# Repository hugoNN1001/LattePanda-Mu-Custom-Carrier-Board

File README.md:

## What is it?
In an attempt to pick up some high-speed PCB skills before jumping onto my own personal high-speed project, I decided to buy a course from Tech Explorations and start from there. The project was a custom carrier board for the LattePanda Mu compute module.

The most important I learned from this project was about differential pairs routing, from sizing traces to the correct impedance depending on the stack-up, to preventing crosstalk, to matching trace length and preventing timing skew, to maintaining continuous reference plan and return path, as well as getting somewhat familiar to high-speed protocols like PCIe, Gbe Ethernet, USB3.9, HDMI, etc.

I have also decided to buy [another course](https://fedevel.com/courses/advanced-digital-hardware-design) on the same topic from Phil's Lab (there goes my wallet). This time, however, I won't be following the course and build a whole FPGA/SOC PCB. Instead, I will be using it as a guide to work on my upcoming project, which is going to be something about eDP or some other protocols to connect my laptop to a bare monitor. Can't wait!

## Status
18/09/2026

I have been grinding on the layout for the past few days. Last night, I let my laptop die without properly saving and closing the PCB editor. When I found out this morning that the layout work I had been working on was completely lost, I quickly checked the backup files.

To my surprise, there was none. I then found out that the automatic backup feature was not enabled. So now I am left with nothing to show for my work. At least now, my only comfort is the stuff I was able to learn about high-speed PCB design throughout this project.

In my original layout, USB3.0/2.0, Ethernet, HDMI, M.2 E&M Key, GPIO, I2C, UART, as well as the PSU had been laid out.

Below are the links to the photos of the schematics and the (old) layout. Somehow the schematic window was able to close down properly before my laptop died so they are up to date.

## Photos
<table>
  <tr>
    <td></td>
    <td></td>
  </tr>
  <tr>
    <td></td>
    <td></td>
  </tr>
  <tr>
    <td></td>
    <td></td>
  </tr>
  <tr>
    <td></td>
    <td></td>
  </tr>
  <tr>
    <td></td>
    <td></td>
  </tr>
  <td></td>
  <td><em>Layout progress at time of loss (unsaved crash - see write-up)</em></td>
</table>

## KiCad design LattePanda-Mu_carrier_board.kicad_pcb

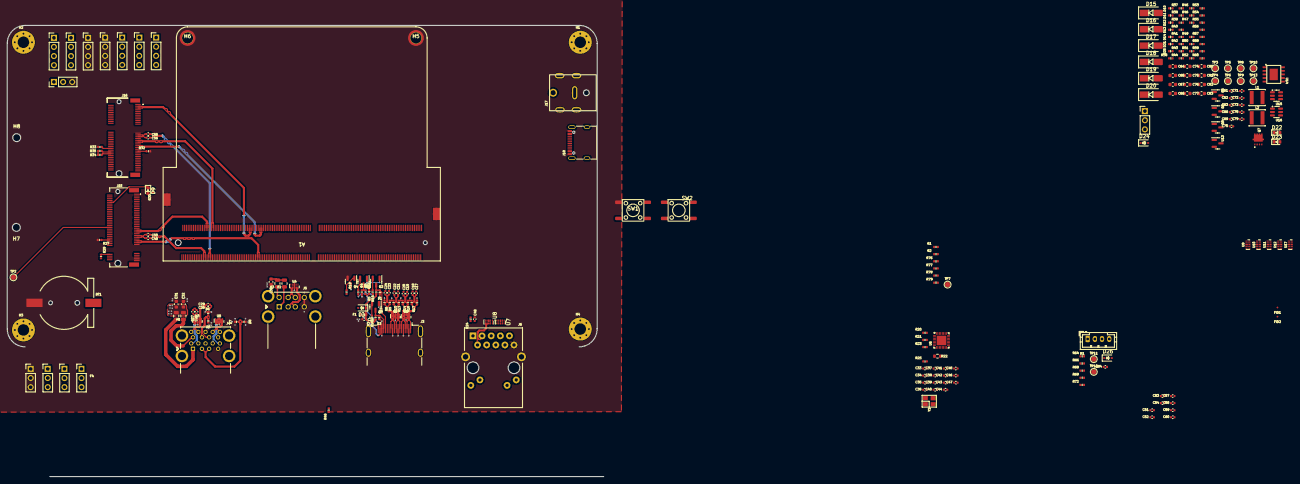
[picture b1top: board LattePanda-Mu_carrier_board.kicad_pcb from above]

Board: 4 copper layers, 240 parts (0 on the bottom side), 179 nets.

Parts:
A1: LattePanda_Mu; LattePanda_Module_H8.0mm_Horizontal
BT1: Battery_Cell; Battery_Holder_CR1220_S8411-45R
C17, C18, C19, C20, C21, C22, C23, C24, C25, C26, C27, C28, C29, C33, C34, C35, C36, C37, C38, C39, C40, C41, C42, C43, C45, C48, C52, C54, C58, C60, C70, C71, C84: 100nF/50V; C_0402_1005Metric
C30, C31, C32, C64, C65, C67, C68, C74, C75, C76, C77, C80, C81, C82, C83: 22uF/10V; C_0603_1608Metric
C44, C51, C53, C57, C59: 10uF/50V; C_0402_1005Metric
C46, C47, C72, C73: 12pF/50V; C_0402_1005Metric
C49, C50, C55, C56: 220nF/50V; C_0402_1005Metric
C61, C62, C63, C66: 1uF/16V; C_0402_1005Metric
C69: 1uF/10V; C_0402_1005Metric
C78, C79: 100nF/10V; C_0402_1005Metric
D1, D2, D3, D5, D6, D7, D8, D10, D11, D21: ESD5V0B03; D_0402_1005Metric
D4, D26: 1N5819WS; D_SOD-323
D9, D22, D23: LED_G; LED_0603_1608Metric
D12, D13, D14: PESD24VS1UL-N; D_0402_1005Metric
D15, D16, D17, D18, D19, D20: SS54; D_SMA
D24: 3V3 Izt=5mA; D_SOD-323
D25: ESD9B5.0ST5G; D_0402_1005Metric
F1: 6V/50mA; C_0603_1608Metric
F2, F3, F4, F5: 6V/1A; Fuse_0805_2012Metric
FID1, FID2: Fiducial; Fiducial_0.5mm_Mask1mm
H1, H2, H3, H4: MountingHole_Pad; MountingHole_3.2mm_M3_Pad_Via
H5, H6: MountingHole_Pad; MountingHole_3mm_M2_Pad_TopOnly
H7, H8: MountingHole_M2.0; MountingHole_2.2mm_M2
J1, J8, J10, J11, J14: Conn_01x03_Pin; PinHeader_1x03_P2.54mm_Vertical
J3: HDMI_A; HDMI_A_Molex_208658-1001_Horizontal
J4: USB3_A_Stacked; USB3_A_Molex_48406-0001_Horizontal_Stacked
J5: USB_A_Stacked; USB_A_CUI_UJ2-ADH-TH_Horizontal_Stacked
J6: RJ45_RB1-125B8G1A; RJ45_UDE_RB1-125B8G1A
J7, J9, J12, J13, J19, J20, J21: Conn_01x04_Pin; PinHeader_1x04_P2.54mm_Vertical
J15: Bus_M.2_Socket_M; PCIe_M.2_Connectors_P=0.5mm_H=4.2mm_KeyM
J16: Bus_M.2_Socket_E; PCIe_M.2_Connectors_P=0.5mm_H=4.2mm_KeyE
J17: Barrel_Jack_Switch; DC_Jack_DC007B_30V_10A
J18: USB_C_Receptacle_USB2.0_16P; USB_C_Receptacle_G-Switch_GT-USB-7010ASV
JP1: SolderJumper_3_Bridged12; PinHeader_1x03_P2.54mm_Vertical
L1, L2: 2.2uH/4.3A; L_Sunlord_SWPA4020S
M1: Fan_4pin; JST_PH_B4B-PH-K_1x04_P2.00mm_Vertical
Q1, Q5, Q6, Q8: 2N7002; SOT-23
Q2, Q3, Q4: 2SK3018; SOT-23
Q7: AON7262E; MOSFET_PDFN8_3.3x3.3
R1, R11, R37, R47: 1k/1%; R_0402_1005Metric
R2, R20, R21, R34, R35, R36, R38, R40, R49, R50, R56, R58, R78, R79: 10k/1%; R_0402_1005Metric
R3, R5, R15, R18, R19, R39, R52, R53: 2.2k/1%; R_0402_1005Metric
R4, R23: 1M/1%; R_0402_1005Metric
R6, R41, R42, R54, R59, R66, R68: 21.5k/1%; R_0402_1005Metric
R7, R8, R9, R10, R13, R14, R16, R17, R24, R25: 470R/1%; R_0402_1005Metric
R22: 2.49k/1%; R_0603_1608Metric
R27, R29, R32, R33: 0R/1%; R_0402_1005Metric
R30: 2.2K/1%; R_0402_1005Metric
R43: 56k/1%; R_0402_1005Metric
R44, R45, R51, R76, R77: 100k/1%; R_0402_1005Metric
R46, R48, R55, R69: 100R/1%; R_0402_1005Metric
R57: 75k/1%; R_0402_1005Metric
R60, R64, R72: 4.7k/1%; R_0402_1005Metric
SW1: PWR_SW; SW_Push_6x6x6
SW2: RST_SW; SW_Push_6x6x6
TP2, TP3, TP4, TP5, TP6, TP7, TP8, TP9, TP10, TP11, TP12, TP13: TestPoint; TestPoint_Pad_D1.5mm
U1, U2: TPAZ1023-04F; Diodes_UDFN-10_1.0x2.5mm_P0.5mm
U3, U9, U10, U11, U12, U17: ULC0524P; Diodes_UDFN-10_1.0x2.5mm_P0.5mm
U4, U5: Diodes_UDFN-10_1.0x2.5mm_P0.5mm
U6: RTL8111H-CG-RH; QFN-32-1EP_4x4mm_P0.4mm_EP2.65x2.65mm
U7, U8: ULC0524P; Diodes_UDFN-10_1x2.5mm_P0.5mm
U13: TL431DBZ; SOT-23
U14: USB PD等快充协议受电芯片-CH224K-ESSOP10; ESSOP-10-1EP_3.9x5mm_P1.0mm_EP3.2x2.3
U15, U16: SY8253ADC; TSOT-23-6
Y1: 25Mhz; Crystal_SMD_3225-4Pin_3.2x2.5mm

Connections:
5V_HDMI_VCC: C25.1, D4.1 (K), F1.1, R15.1, R18.1
+1V0: C33.1, C34.1, C35.1, C36.1, C40.1, C44.1, U6.3 (AVDD10), U6.8 (AVDD10), U6.22 (DVDD10), U6.24 (REGOUT), U6.30 (AVDD10)
+3.3V: C37.1, C41.1, C45.1, C51.1, C52.1, C53.1, C54.1, C57.1, C58.1, C59.1, C60.1, C73.2, C75.2, C77.2, C79.2, C81.2, C83.2, J13.1, J13.2, J13.3, J13.4, J14.1, J14.2, J14.3, J15.2 (3.3V), J15.4 (3.3V), J15.12 (3.3V), J15.14 (3.3V), J15.16 (3.3V), J15.18 (3.3V), J15.70 (3.3V), J15.72 (3.3V), J15.74 (3.3V), J16.2 (3.3V), J16.4 (3.3V), J16.72 (3.3V), J16.74 (3.3V), J21.1, J21.2, J21.3, J21.4, L2.2, Q1.1 (G), Q2.1 (G), Q3.1 (G), R3.1, R4.2, R5.1, R20.2, R21.2, R24.2, R25.2, R30.2, R34.1, R35.1, R50.2, R52.2, R56.2, R59.2, R64.2, TP6.1 (1_1), U6.11 (AVDD33), U6.23 (VDDREG), U6.32 (AVDD33)
+5V: C30.1, C31.1, C32.1, C72.2, C74.2, C76.2, C78.2, C80.2, C82.2, C84.1, D4.2 (A), D26.1 (K), F2.2, F3.2, F4.2, F5.2, L1.2, M1.2 (+), R57.2, R72.1, TP5.1 (1_1)
+12V: C63.1, D15.2 (A), D16.2 (A), D17.2 (A), J17.1, Q7.1 (S_1), Q7.2 (S_2), Q7.3 (S_3), R38.2, R40.1, R44.1, TP4.1 (1_1)
+12VA: Q7.5 (D_1), Q7.6 (D_2), Q7.7 (D_3), Q7.8 (D_4), Q7.9 (D_5), Q7.10 (D_6), Q7.11 (D_7), R54.2, TP8.1 (1_1)
+15V: D14.1 (K), D18.2 (A), D19.2 (A), D20.2 (A), J18.A4 (VBUS), J18.A9 (VBUS), J18.B4 (VBUS), J18.B9 (VBUS), R36.1, R37.1, TP3.1 (1_1)
+BATT: A1.115 (VBAT), R1.1
/Fan/FAN1_PWM: A1.2 (FAN1_PWM), R64.1, R69.1, TP12.1 (1_1)
/Fan/FAN1_TAC: A1.4 (FAN1_TAC), R66.1, R68.1, TP11.1 (1_1)
/GPIO/GPP_D0: A1.128 (GPP_D0), J19.1, U17.1
/GPIO/GPP_D1: A1.130 (GPP_D1), J19.2, U17.2
/GPIO/GPP_D2: A1.132 (GPP_D2), J19.3, U17.4
/GPIO/GPP_D3: A1.134 (GPP_D3), J19.4, U17.5
/GPIO/I2C2_SCL: A1.154 (I2C2_SCL), J9.1, U11.1
/GPIO/I2C2_SDA: A1.156 (I2C2_SDA), J7.1, U9.1
/GPIO/I2C3_SCL: A1.150 (I2C3_SCL), J9.2, U11.2
/GPIO/I2C3_SDA: A1.152 (I2C3_SDA), J7.2, U9.2
/GPIO/I2C4_SCL: A1.146 (I2C4_SCL), J9.3, U11.4
/GPIO/I2C4_SDA: A1.148 (I2C4_SDA), J7.3, U9.4
/GPIO/I2C5_SCL: A1.142 (I2C5_SCL), J9.4, U11.5
/GPIO/I2C5_SDA: A1.144 (I2C5_SDA), J7.4, U9.5
/GPIO/SOC_UART0_RX: A1.137 (UART0_RXD), J8.1, U10.1, U12.1
/GPIO/SOC_UART0_TX: A1.139 (UART0_TXD), J10.1
/GPIO/SOC_UART1_RX: A1.141 (UART1_RXD), J8.2, U10.2, U12.2
/GPIO/SOC_UART1_TX: A1.143 (UART1_TXD), J10.2
/GPIO/SOC_UART2_RX: A1.140 (UART2_RXD), J8.3, U10.4, U12.4
/GPIO/SOC_UART2_TX: A1.138 (UART2_TXD), J10.3
/Gigabit Ethernet/GbE_PCIe_CLK+: A1.94 (REFCLK4+), U6.15 (REFCLK_P)
/Gigabit Ethernet/GbE_PCIe_CLK-: A1.96 (REFCLK4-), U6.16 (REFCLK_N)
/Gigabit Ethernet/GbE_PCIe_RX+: A1.64 (HSIO6_RX+), C43.1
/Gigabit Ethernet/GbE_PCIe_RX-: A1.66 (HSIO6_RX-), C39.1
/Gigabit Ethernet/GbE_PCIe_TX+: A1.61 (HSIO6_TX+), C42.1
/Gigabit Ethernet/GbE_PCIe_TX-: A1.63 (HSIO6_TX-), C38.1
/Gigabit Ethernet/HSI+: C42.2, U6.13 (HSIP)
/Gigabit Ethernet/HSI-: C38.2, U6.14 (HSIN)
/Gigabit Ethernet/HSO+: C43.2, U6.17 (HSOP)
/Gigabit Ethernet/HSO-: C39.2, U6.18 (HSON)
/Gigabit Ethernet/MDI0+: J6.R2 (TD1+), U6.1 (MDIP0), U8.5, U8.6 (NC)
/Gigabit Ethernet/MDI0-: J6.R3 (TD1-), U6.2 (MDIN0), U8.4, U8.7 (NC)
/Gigabit Ethernet/MDI1+: J6.R4 (TD2+), U6.4 (MDIP1), U8.2, U8.9 (NC)
/Gigabit Ethernet/MDI1-: J6.R5 (TD2-), U6.5 (MDIN1), U8.1, U8.10 (NC)
/Gigabit Ethernet/MDI2+: J6.R6 (TD3+), U6.6 (MDIP2), U7.5, U7.6 (NC)
/Gigabit Ethernet/MDI2-: J6.R7 (TD3-), U6.7 (MDIN2), U7.4, U7.7 (NC)
/Gigabit Ethernet/MDI3+: J6.R8 (TD4+), U6.9 (MDIP3), U7.2, U7.9 (NC)
/Gigabit Ethernet/MDI3-: J6.R9 (TD4-), U6.10 (MDIN3), U7.1, U7.10 (NC)
/HDMI/DDC_SCL: D1.2 (A2), J3.15 (SCL), Q2.3 (D), R15.2
/HDMI/DDC_SDA: D3.2 (A2), J3.16 (SDA), Q3.3 (D), R18.2
/HDMI/DDIB_HPD: A1.183 (DDIB_HPD), Q1.2 (S), R4.1
/HDMI/DDIB_TX0+: A1.217 (DDIB_TX0+), C17.1
/HDMI/DDIB_TX0-: A1.215 (DDIB_TX0-), C18.1
/HDMI/DDIB_TX1+: A1.211 (DDIB_TX1+), C19.1
/HDMI/DDIB_TX1-: A1.209 (DDIB_TX1-), C20.1
/HDMI/DDIB_TX2+: A1.205 (DDIB_TX2+), C21.1
/HDMI/DDIB_TX2-: A1.203 (DDIB_TX2-), C22.1
/HDMI/DDIB_TX3+: A1.199 (DDIB_TX3+), C23.1
/HDMI/DDIB_TX3-: A1.197 (DDIB_TX3-), C24.1
/HDMI/DDI_B_DDC_SCL: A1.171 (DDIB_DDC_SCL), Q2.2 (S), R5.2
/HDMI/DDI_B_DDC_SDA: A1.169 (DDIB_DDC_SDA), Q3.2 (S), R3.2
/HDMI/HPD: D2.2 (A2), J3.19 (HPD), R11.2
/HDMI/TMDS_CK+: C23.2, J3.10 (CK+), R8.1, U2.4, U2.7 (NC)
/HDMI/TMDS_CK-: C24.2, J3.12 (CK-), R7.1, U2.5, U2.6 (NC)
/HDMI/TMDS_D0+: C21.2, J3.7 (D0+), R10.1, U2.1, U2.10 (NC)
/HDMI/TMDS_D0-: C22.2, J3.9 (D0-), R9.1, U2.2, U2.9 (NC)
/HDMI/TMDS_D1+: C19.2, J3.4 (D1+), R14.1, U1.4, U1.7 (NC)
/HDMI/TMDS_D1-: C20.2, J3.6 (D1-), R13.1, U1.5, U1.6 (NC)
/HDMI/TMDS_D2+: C17.2, J3.1 (D2+), R17.1, U1.1, U1.10 (NC)
/HDMI/TMDS_D2-: C18.2, J3.3 (D2-), R16.1, U1.2, U1.9 (NC)
/LattePanda Mu Module/HSIO_0_TX+: A1.13 (HSIO0_TX+), C27.2
/LattePanda Mu Module/HSIO_0_TX-: A1.15 (HSIO0_TX-), C26.2
/LattePanda Mu Module/HSIO_1_TX+: A1.19 (HSIO1_TX+), C29.2
/LattePanda Mu Module/HSIO_1_TX-: A1.21 (HSIO1_TX-), C28.2
/LattePanda Mu Module/HSIO_2_RX+: A1.28 (HSIO2_RX+), J15.43 (PERp0/SATA-B-)
/LattePanda Mu Module/HSIO_2_RX-: A1.30 (HSIO2_RX-), J15.41 (PERn0/SATA-B+)
/LattePanda Mu Module/HSIO_2_TX+: A1.25 (HSIO2_TX+), C49.1
/LattePanda Mu Module/HSIO_2_TX-: A1.27 (HSIO2_TX-), C50.1
/LattePanda Mu Module/HSIO_3_RX+: A1.34 (HSIO3_RX+), J16.43 (PERn0)
/LattePanda Mu Module/HSIO_3_RX-: A1.36 (HSIO3_RX-), J16.41 (PERp0)
/LattePanda Mu Module/HSIO_3_TX+: A1.31 (HSIO3_TX+), C56.1
/LattePanda Mu Module/HSIO_3_TX-: A1.33 (HSIO3_TX-), C55.1
/LattePanda Mu Module/REFCLK0+: A1.85 (REFCLK0+), J15.55 (REFCLKp)
/LattePanda Mu Module/REFCLK0-: A1.87 (REFCLK0-), J15.53 (REFCLKn)
/LattePanda Mu Module/REFCLK3+: A1.88 (REFCLK3+), J16.47 (REFCLKp0)
/LattePanda Mu Module/REFCLK3-: A1.90 (REFCLK3-), J16.49 (REFCLKn0)
/LattePanda Mu Module/SLS_S3: A1.7 (SLS_S3), JP1.3 (B)
/LattePanda Mu Module/SUSCLK_WIFI: A1.131 (SUSCLK), R29.2
/LattePanda Mu Module/USB2_P7+: A1.76 (USB2_P7+), J16.3 (USB_D+)
/LattePanda Mu Module/USB2_P7-: A1.78 (USB2_P7-), J16.5 (USB_D-)
/LattePanda Mu Module/~PWR_SW: A1.1 (~PWRBTN), R48.2
/LattePanda Mu Module/~RST_SW: A1.3 (~RSTBTN), R55.2
/M.2 M Key/CON_PCIE_TX0+: C55.2, J16.35 (PETp0)
/M.2 M Key/CON_PCIE_TX0-: C56.2, J16.37 (PETn0)
/M.2 M Key/CON_PCIE_TX1+: C49.2, J15.49 (PETp0/SATA-A+)
/M.2 M Key/CON_PCIE_TX1-: C50.2, J15.47 (PETn0/SATA-A-)
/M.2 M Key/~CLKREQ_E: J16.53 (~CLKREQ0), R32.1
/M.2 M Key/~CLKREQ_M: J15.52 (~CLKREQ), R27.1
/Power Supply/CC1: D13.1 (K), J18.A5 (CC1), U14.7 (CC1)
/Power Supply/CC2: D12.1 (K), J18.B5 (CC2), U14.6 (CC2)
/Power Supply/PWR_C_D+: D11.2 (A2), J18.A7 (D-), J18.B7 (D-), U14.5 (DM)
/Power Supply/PWR_C_D-: D10.2 (A2), J18.A6 (D+), J18.B6 (D+), U14.4 (DP)
/Power Supply/PWR_EN: Q6.1 (G), R46.1, R51.2, TP9.1 (1_1), U15.4 (EN), U16.4 (EN)
/USB 2.0 &3.0/CON_USB1_D_N: A1.109 (USB2_P5-), J5.2 (D1-), U4.2, U4.9 (NC)
/USB 2.0 &3.0/CON_USB1_D_P: A1.111 (USB2_P5+), J5.3 (D1+), U4.1, U4.10 (NC)
/USB 2.0 &3.0/CON_USB2_D_N: A1.79 (USB2_P3-), J5.6 (D2-), U4.5, U4.6 (NC)
/USB 2.0 &3.0/CON_USB2_D_P: A1.81 (USB2_P3+), J5.7 (D2+), U4.4, U4.7 (NC)
/USB 2.0 &3.0/CON_USB3_D_N: A1.75 (USB2_P2+), D8.2 (A2), J4.2 (D1-)
/USB 2.0 &3.0/CON_USB3_D_P: A1.73 (USB2_P2-), D7.2 (A2), J4.3 (D1+)
/USB 2.0 &3.0/CON_USB3_SSRX_N: A1.18 (HSIO0_RX-), J4.5 (SSRX1-), U5.4, U5.7 (NC)
/USB 2.0 &3.0/CON_USB3_SSRX_P: A1.16 (HSIO0_RX+), J4.6 (SSRX1+), U5.5, U5.6 (NC)
/USB 2.0 &3.0/CON_USB3_SSTX_N: C26.1, J4.8 (SSTX1-), U3.4, U3.7 (NC)
/USB 2.0 &3.0/CON_USB3_SSTX_P: C27.1, J4.9 (SSTX1+), U3.5, U3.6 (NC)
/USB 2.0 &3.0/CON_USB4_D_N: A1.67 (USB2_P1-), D6.2 (A2), J4.11 (D2-)
/USB 2.0 &3.0/CON_USB4_D_P: A1.69 (USB2_P1+), D5.2 (A2), J4.12 (D2+)
/USB 2.0 &3.0/CON_USB4_SSRX_N: A1.24 (HSIO1_RX-), J4.14 (SSRX2-), U5.1, U5.10 (NC)
/USB 2.0 &3.0/CON_USB4_SSRX_P: A1.22 (HSIO1_RX+), J4.15 (SSRX2+), U5.2, U5.9 (NC)
/USB 2.0 &3.0/CON_USB4_SSTX_N: C28.1, J4.17 (SSTX2-), U3.1, U3.10 (NC)
/USB 2.0 &3.0/CON_USB4_SSTX_P: C29.1, J4.18 (SSTX2+), U3.2, U3.9 (NC)
/~PE_WAKE: A1.103 (~WAKE), J15.54 (~PEWAKE), J16.55 (~PEWAKE0)
/~PLT_RST: A1.105 (~PLTRST), J15.50 (~PERST), J16.52 (~PERST0), U6.19 (PERSTB)
/~PWR_LED/~PSON: A1.5 (SLS_S0), JP1.1 (A), R19.2, R47.1
GND: A1.11 (GND), A1.14 (GND), A1.17 (GND), A1.20 (GND), A1.23 (GND), A1.26 (GND), A1.29 (GND), A1.32 (GND), A1.35 (GND), A1.38 (GND), A1.41 (GND), A1.44 (GND), A1.47 (GND), A1.50 (GND), A1.53 (GND), A1.56 (GND), A1.59 (GND), A1.62 (GND), A1.65 (GND), A1.68 (GND), A1.71 (GND), A1.74 (GND), A1.77 (GND), A1.80 (GND), A1.83 (GND), A1.86 (GND), A1.89 (GND), A1.92 (GND), A1.95 (GND), A1.98 (GND), A1.101 (GND), A1.107 (GND), A1.110 (GND), A1.113 (GND), A1.116 (GND), A1.135 (GND), A1.136 (GND), A1.151 (GND), A1.158 (GND), A1.167 (GND), A1.170 (GND), A1.181 (GND), A1.182 (GND), A1.187 (TCP0_HPD), A1.188 (GND), A1.189 (GND), A1.194 (GND), A1.195 (GND), A1.200 (GND), A1.201 (GND), A1.206 (GND), A1.207 (GND), A1.212 (GND), A1.213 (GND), A1.218 (GND), A1.219 (GND), A1.224 (GND), A1.225 (GND), A1.230 (GND), A1.231 (GND), A1.236 (GND), A1.237 (GND), A1.242 (GND), A1.243 (GND), A1.248 (GND), A1.249 (GND), A1.MP (Mountinge_Pads), BT1.2 (-), C25.2, C30.2, C31.2, C32.2, C33.2, C34.2, C35.2, C36.2, C37.2, C40.2, C41.2, C44.2, C45.2, C46.2, C47.2, C48.1, C51.2, C52.2, C53.2, C54.2, C57.2, C58.2, C59.2, C60.2, C61.2, C62.2, C64.2, C65.1, C66.1, C67.2, C68.1, C69.1, C74.1, C75.1, C76.1, C77.1, C78.1, C79.1, C80.1, C81.1, C82.1, C83.1, C84.2, D1.1 (A1), D2.1 (A1), D3.1 (A1), D5.1 (A1), D6.1 (A1), D7.1 (A1), D8.1 (A1), D10.1 (A1), D11.1 (A1), D12.2 (A), D13.2 (A), D14.2 (A), D21.1 (A1), D23.1 (K), D24.2 (A), D25.1 (A1), H1.1 (1_1), H2.1 (1_1), H3.1 (1_1), H4.1 (1_1), H5.1 (1_1), H6.1 (1_1), J1.3, J3.2 (D2S), J3.5 (D1S), J3.8 (D0S), J3.11 (CKS), J3.17 (GND), J3.SH, J4.4 (GND1), J4.7 (DRAIN1), J4.13 (GND2), J4.16 (DRAIN2), J5.4 (GND1), J5.8 (GND2), J6.R10 (GND), J6.SH, J11.1, J11.2, J11.3, J12.1, J12.2, J12.3, J12.4, J15.1 (GND), J15.3 (GND), J15.9 (GND), J15.15 (GND), J15.21 (GND), J15.27 (GND), J15.33 (GND), J15.39 (GND), J15.45 (GND), J15.51 (GND), J15.57 (GND), J15.71 (GND), J15.73 (GND), J15.75 (GND), J16.1 (GND), J16.7 (GND), J16.18 (GND), J16.33 (GND), J16.39 (GND), J16.45 (GND), J16.51 (GND), J16.57 (GND), J16.63 (GND), J16.69 (GND), J16.75 (GND), J17.2, J17.3, J18.A1 (GND), J18.A12 (GND), J18.B1 (GND), J18.B12 (GND), J20.1, J20.2, J20.3, J20.4, M1.1 (-), Q4.2 (S), Q6.2 (S), Q8.2 (S), R6.2, R22.1, R27.2, R32.2, R33.2, R39.1, R42.1, R43.2, R49.1, R51.1, R58.1, R60.1, R66.2, R76.1, R76.2, R77.1, R78.2, R79.2, SW1.1, SW2.1, U1.3 (VSS), U1.8 (VSS), U2.3 (VSS), U2.8 (VSS), U3.3 (VSS), U3.8 (VSS), U4.3 (VSS), U4.8 (VSS), U5.3 (VSS), U5.8 (VSS), U6.33 (GND), U7.3 (VSS), U7.8 (VSS), U8.3 (VSS), U8.8 (VSS), U9.3 (VSS), U9.8 (VSS), U10.3 (VSS), U10.8 (VSS), U11.3 (VSS), U11.8 (VSS), U12.3 (VSS), U12.8 (VSS), U13.3 (A), U14.0 (GND), U15.2 (GND), U16.2 (GND), U17.3 (VSS), U17.8 (VSS), Y1.2 (G), Y1.4 (G)
unnamed: A1.12 (SIO_UART_RX), J1.2
unnamed: A1.10 (SIO_UART_TX), J1.1
unnamed: A1.185 (TCP1_HPD), R77.2
unnamed: A1.133 (~BIOS_SEL), R2.1, TP7.1 (1_1)
unnamed: A1.100 (~CLKREQ3), R78.1
unnamed: A1.102 (~CLKREQ4), R79.1
unnamed: BT1.1 (+), R1.2
unnamed: D9.2 (A), R30.1
unnamed: D9.1 (K), J15.10 (DAS/~DSS/~LED1)
unnamed: C66.2, D21.2 (A2), R48.1, R50.1, SW1.2
unnamed: D22.2 (A), R52.1
unnamed: D22.1 (K), Q8.3 (D)
unnamed: D23.2 (A), R54.1
unnamed: C69.2, D25.2 (A2), R55.1, R56.1, SW2.2
unnamed: D26.2 (A), M1.3 (Tacho), R68.2, R72.2
unnamed: F1.2, J3.18 (+5V)
unnamed: F4.1, J4.1 (VBUS1)
unnamed: F5.1, J4.10 (VBUS2)
unnamed: F2.1, J5.1 (VBUS1)
unnamed: F3.1, J5.5 (VBUS2)
unnamed: C48.2, J6.R1 (CT)
unnamed: J6.L1, R25.1
unnamed: J6.L3, R24.1
unnamed: J15.38 (DEVSLP), TP2.1 (1_1)
unnamed: J15.68 (SUSCLK), R29.1
unnamed: J16.50 (SUSCLK), R33.1
unnamed: J16.56 (~W_DISABLE1), R34.2
unnamed: J16.54 (~W_DISABLE2), R35.2
unnamed: JP1.2 (C), R46.2
unnamed: M1.4 (PWM), R69.2
unnamed: Q1.3 (D), R6.1, R11.1
unnamed: Q4.3 (D), R7.2, R8.2, R9.2, R10.2, R13.2, R14.2, R16.2, R17.2
unnamed: Q4.1 (G), R19.1
unnamed: Q5.3 (D), R45.1
unnamed: C62.1, Q5.1 (G), R41.2, R42.2
unnamed: Q5.2 (S), Q6.3 (D)
unnamed: C63.2, Q7.4 (G), R44.2, R45.2
unnamed: Q8.1 (G), R47.2, R49.2
unnamed: C47.1, R23.1, U6.28 (CKXTAL1), Y1.1
unnamed: C46.1, R23.2, U6.29 (CKXTAL2), Y1.3
unnamed: R20.1, U6.20 (ISOLATEB)
unnamed: R21.1, U6.21 (LANWAKEB)
unnamed: J6.L4, U6.26 (LED1)
unnamed: J6.L2, U6.25 (LED2)
unnamed: R22.2, U6.31 (RSET)
unnamed: R40.2, R41.1, U13.1 (K)
unnamed: R38.1, R39.2, U13.2 (REF)
unnamed: R43.1, U14.9 (CFG1)
unnamed: R36.2, U14.8 (VBUS)
unnamed: C61.1, R37.2, U14.1 (VDD)
unnamed: C70.1, U15.1 (BOOST)
unnamed: C72.1, R57.1, R58.2, U15.3 (FB)
unnamed: C70.2, L1.1, U15.6 (SW)
unnamed: C71.1, U16.1 (BOOST)
unnamed: C73.1, R59.1, R60.2, U16.3 (FB)
unnamed: C71.2, L2.1, U16.6 (SW)
VDC: A1.250 (VIN), A1.251 (VIN), A1.252 (VIN), A1.253 (VIN), A1.254 (VIN), A1.255 (VIN), A1.256 (VIN), A1.257 (VIN), A1.258 (VIN), A1.259 (VIN), A1.260 (VIN), C64.1, C65.2, C67.1, C68.2, D15.1 (K), D16.1 (K), D17.1 (K), D18.1 (K), D19.1 (K), D20.1 (K), R53.2, TP10.1 (1_1), U15.5 (VIN), U16.5 (VIN)
VPullup: D24.1 (K), R53.1, TP13.1 (1_1)
